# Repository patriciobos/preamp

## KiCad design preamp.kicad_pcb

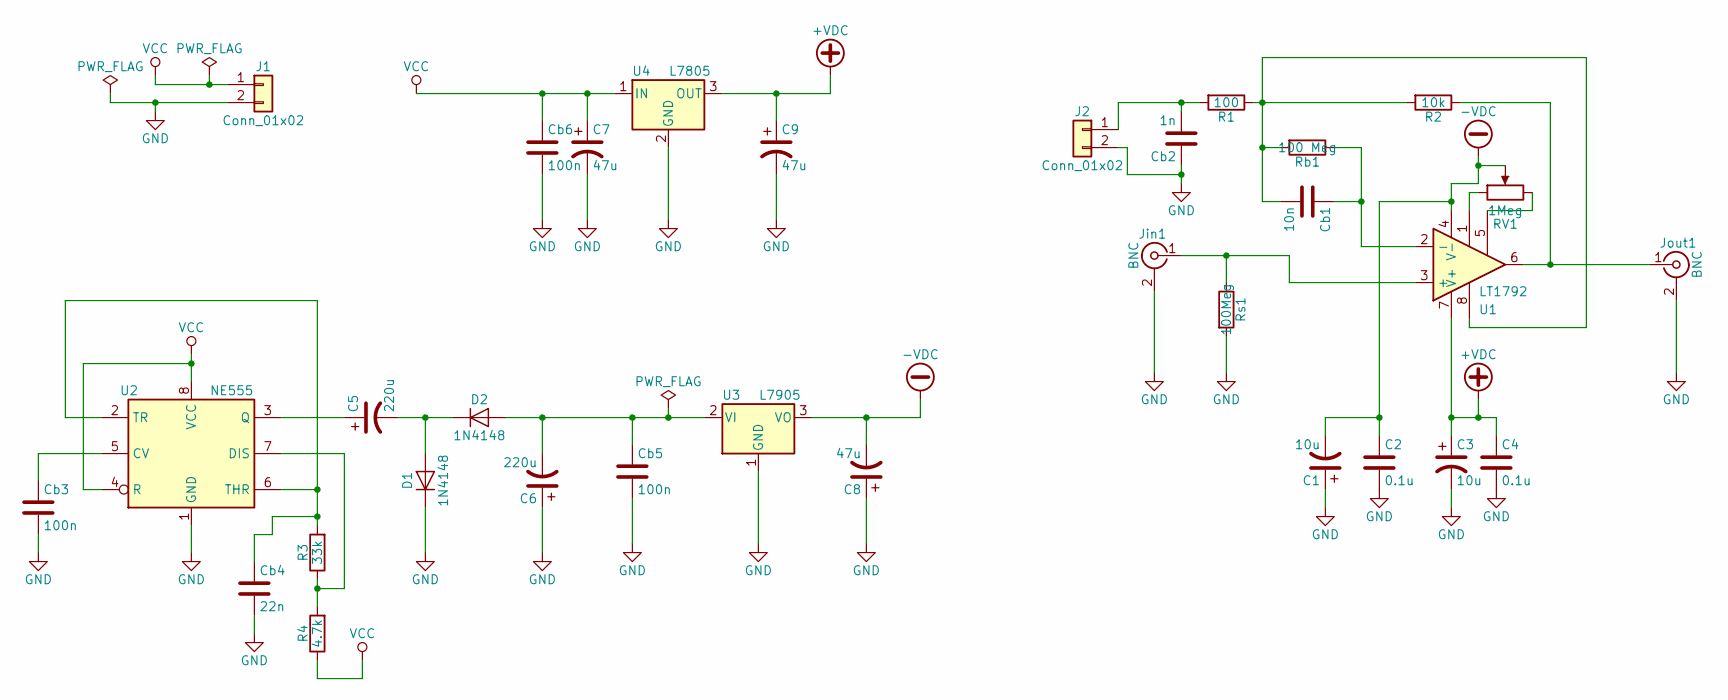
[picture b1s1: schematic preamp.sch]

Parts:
C1, C3: 10u; CP_Radial_Tantal_D5.0mm_P2.50mm
C2, C4: 0.1u; CP_Radial_Tantal_D4.5mm_P2.50mm
C5, C6: 220u; CP_Radial_D10.0mm_P5.00mm
C7, C8, C9: 47u; CP_Radial_Tantal_D7.0mm_P5.00mm
Cb1: 10n; CP_Radial_Tantal_D4.5mm_P2.50mm
Cb2: 1n; C_Radial_D8.0mm_H11.5mm_P3.50mm
Cb3: 100n; C_Disc_D5.0mm_W2.5mm_P5.00mm
Cb4: 22n; CP_Radial_Tantal_D4.5mm_P2.50mm
Cb5, Cb6: 100n; CP_Radial_Tantal_D4.5mm_P2.50mm
D1, D2: 1N4148; D_T-1_P5.08mm_Horizontal
J1: Conn_01x02; PhoenixContact_MC-GF_02x3.50mm_Angled_ThreadedFlange_MountH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
J2: Conn_01x02; Socket_Strip_Straight_1x02_Pitch2.54mm
Jin1: BNC; BNC_Socket_TYCO-AMP_LargePads
Jout1: BNC; BNC_Socket_TYCO-AMP_LargePads
R1: 100; R_Axial_DIN0204_L3.6mm_D1.6mm_P5.08mm_Horizontal
R2: 10k; R_Axial_DIN0204_L3.6mm_D1.6mm_P5.08mm_Horizontal
R3: 33k; R_Axial_DIN0204_L3.6mm_D1.6mm_P5.08mm_Horizontal
R4: 4.7k; R_Axial_DIN0204_L3.6mm_D1.6mm_P5.08mm_Horizontal
RV1: 1Meg; Potentiometer_Trimmer_Bourns_3296W
Rb1: 100 Meg; R_Axial_DIN0204_L3.6mm_D1.6mm_P7.62mm_Horizontal
Rs1: 100Meg; R_Axial_DIN0204_L3.6mm_D1.6mm_P7.62mm_Horizontal
U1: LT1792; DIP-8_W7.62mm
U2: NE555; DIP-8_W7.62mm
U3: L7905; TO-220-3_Vertical
U4: L7805; TO-220-3_Vertical

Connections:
+VDC: C3.1, C4.1, C9.1, U1.7 (V+), U4.3 (OUT)
-VDC: C1.2, C2.1, C8.2, RV1.2, U1.4 (V-), U3.3 (VO)
GND: C1.1, C2.2, C3.2, C4.2, C6.1, C7.2, C8.1, C9.2, Cb2.1, Cb3.2, Cb4.2, Cb5.2, Cb6.2, D1.1 (K), J1.2, J2.2, Jin1.2 (Ext), Jout1.2 (Ext), Rs1.2, U2.1 (GND), U3.1 (GND), U4.2 (GND)
unnamed: C5.1, U2.3 (Q)
unnamed: C5.2, D1.2 (A), D2.1 (K)
unnamed: C6.2, Cb5.1, D2.2 (A), U3.2 (VI)
unnamed: Cb1.1, Rb1.1, U1.2 (-)
unnamed: Cb1.2, R1.1, R2.2, Rb1.2, U1.8
unnamed: Cb2.2, J2.1, R1.2
unnamed: Cb3.1, U2.5 (CV)
unnamed: Cb4.1, R3.2, U2.2 (TR), U2.6 (THR)
unnamed: Jin1.1 (In), Rs1.1, U1.3 (+)
unnamed: Jout1.1 (In), R2.1, U1.6
unnamed: R3.1, R4.2, U2.7 (DIS)
unnamed: RV1.1, U1.1
unnamed: RV1.3, U1.5
VCC: C7.1, Cb6.1, J1.1, R4.1, U2.4 (R), U2.8 (VCC), U4.1 (IN)

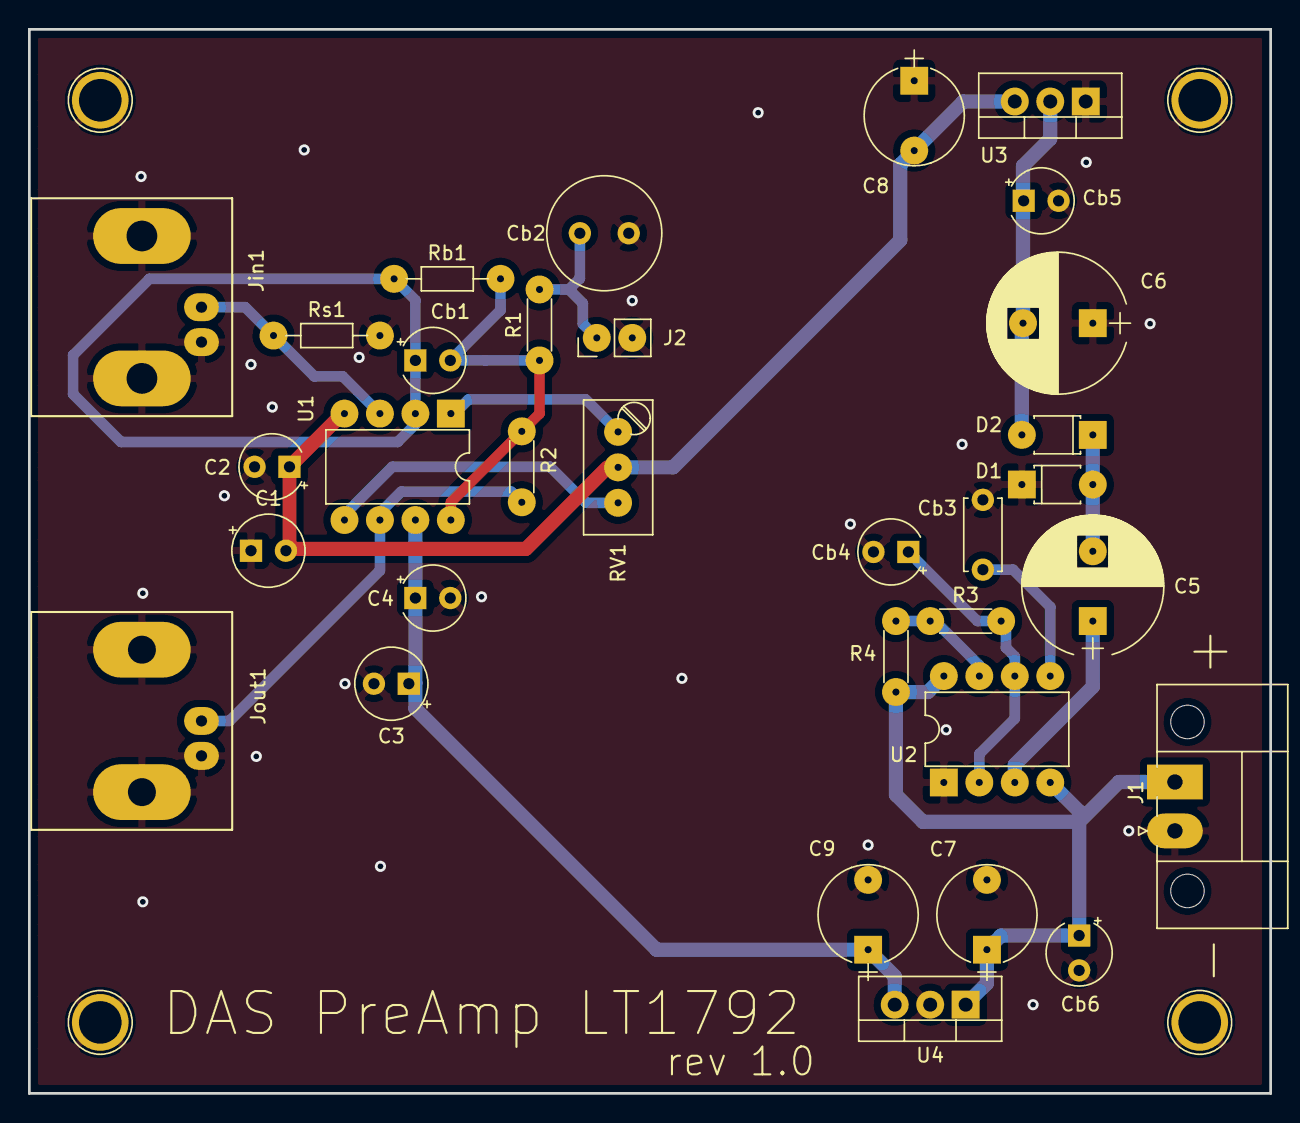
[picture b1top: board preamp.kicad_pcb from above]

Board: 2 copper layers, 88.9 x 76.2 mm, 32 parts (0 on the bottom side), 17 nets.

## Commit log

2021-02-11 primer commit con archivos de rev 1.0
